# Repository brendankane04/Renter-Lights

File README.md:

# Renter Lights

Automatic light control which doesn't involve messing with your light switches & talking to your landlords

# Firmware 

## Files

**Wifi_Interface.cpp:** Driver to send TCP messages over wifi<br>
**SG90.cpp:** Driver for the SG90 servo, turns it on & off.<br>
**SR501.cpp:** Driver the SR501 PIR sensor. The handler init is can be run independently.<br>
**MQTT.cpp:** Initialization for MQTT events & central event handler.<br>
**pins.h:** definitions of relevant GPIO pins.<br>
**main.cpp:** main file. Combines all the modules.<br>

# Hardware

**Hardware.sch:** The schematics for the minimum unit<br>
**Hardware.kicad_pcb:** The layout file<br>

# Mechanical

# Backend

A mosquitto MQTT broker server on a raspberry pi is used to interface the devicecs. Just get one up & running.

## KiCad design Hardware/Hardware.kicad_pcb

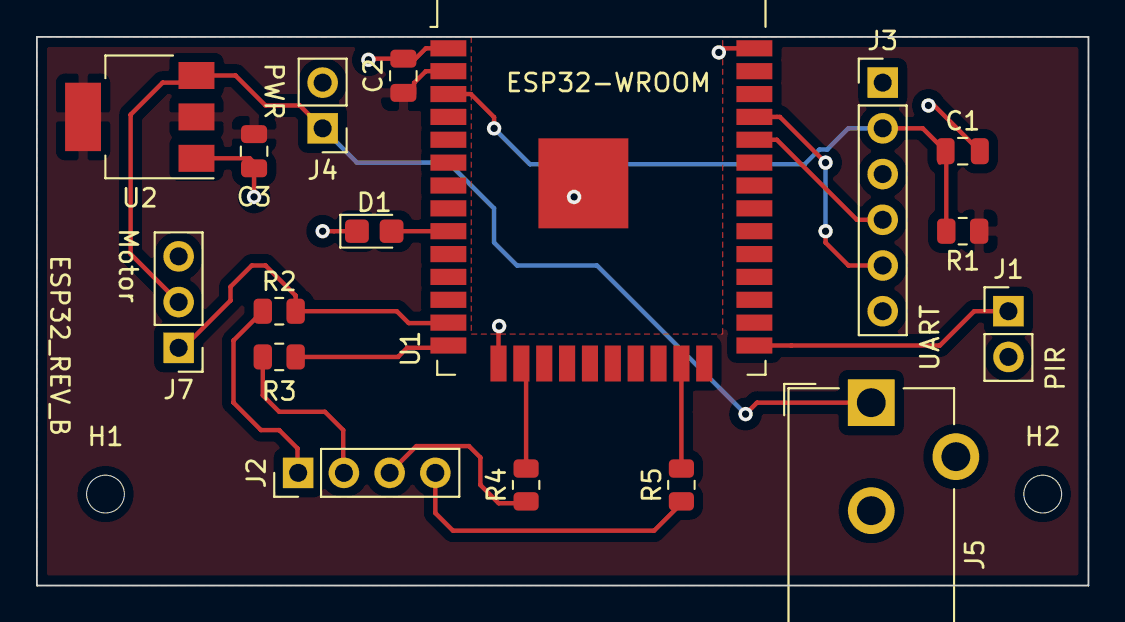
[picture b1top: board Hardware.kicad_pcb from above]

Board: 2 copper layers, 58.4 x 30.5 mm, 19 parts (0 on the bottom side), 16 nets.

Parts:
C1, C3: 0.1uF; C_0805_2012Metric
C2: 1uF; C_0805_2012Metric
D1: LED; LED_0805_2012Metric_Castellated
H1, H2: MountingHole; MountingHole_2.1mm
J1, J4: Conn_01x02; PinHeader_1x02_P2.54mm_Vertical
J2: Conn_01x04; PinHeader_1x04_P2.54mm_Vertical
J3: Conn_01x06; PinHeader_1x06_P2.54mm_Vertical
J5: Jack-DC; BarrelJack_CUI_PJ-102AH_Horizontal
J7: Conn_01x03; PinHeader_1x03_P2.54mm_Vertical
R1: 10K; R_0805_2012Metric
R2, R3, R4, R5: 100; R_0805_2012Metric
U1: ESP32-WROOM-32
U2: AMS1117-3.3; SOT-223-3_TabPin2

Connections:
/BATT_POS: J4.1, J5.1, J7.2, U2.3
/EN: C1.1, J3.2, R1.2, U1.3
/IO33: D1.2, U1.9
/MTCK: R4.2, U1.16
/MTDI: R3.2, U1.14
/MTDO: R5.2, U1.23
/MTMS: J7.1, R2.2, U1.13
/PIR_INPUT: J1.1, U1.25
/RXD: J3.4, U1.34
/TXD: J3.5, U1.35
/VDD33: C2.1, C3.1, R1.1, U1.2, U2.2
GND: C1.2, C2.2, C3.2, D1.1, J1.2, J3.1, J4.2, J5.2, J7.3, U1.1, U1.15, U1.38, U1.39, U2.1
unnamed: J2.1, R2.1
unnamed: J2.2, R3.1
unnamed: J2.3, R4.1
unnamed: J2.4, R5.1

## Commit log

2021-08-12 The README was made.
2021-08-17 The README was updated.
2021-08-29 A reference project/environment was added.
2021-08-30 Build experimenting was done.
2021-08-31 Quality of life improvements were made.
2021-09-01 Stepper motor testing was done.
2021-09-02 Servo control was added.
2021-09-03 The PIR sensor was tested.
2021-09-04 The servo code was simplified.
2021-09-05 Some basic control code was created.
2021-09-06 A basic control set of code was added.
2021-09-07 Servo code was exported.
2021-09-07 The class was finished.
2021-09-08 The build files were removed from the index.
2021-09-08 The SG90 driver was cleaned up.
2021-09-08 The SR501 driver was added.
2021-09-08 The gitignore was altered to ignore the build files.
2021-09-09 The project was converted to an eclipse IDF project to assist development.
2021-09-09 The build files will now be ignored.
2021-09-09 The original source directory was removed.
2021-09-10 The wifi interface was started.
2021-09-11 A datasheet was added to the PIR header file.
2021-09-12 The README was restored.
2021-09-13 The wifi driver was developed.
2021-09-13 The wifi driver was completed writing-wise, awaiting testing.
2021-09-15 Errors were removed from the wifi driver.
2021-09-16 A bug in the wifi was fixed.
2021-09-17 Wifi development was done.
2021-09-19 An extraneous file was removed.
2021-09-20 SOME version of a wrapper class was added. OMG, that was a waste of time.
2021-09-21 lwIP updates
2021-09-21 README update.
2021-09-23 A socket init was added.
2021-09-24 Eclipse settings
2021-09-25 Socket dev
2021-09-26 Some kinks were worked out.
2021-09-26 The send function was integrated. A lookover & rewrite is still necessary though. It's so messy.
2021-09-28 Wifi driver maintenance
2021-09-30 Wifi driver updates
2021-09-30 Error correction
2021-10-01 A streamlined wifi setup was added.
2021-10-01 Comments were added.
2021-10-02 Testing was done. Comments were added.
2021-10-03 Driver updates & testing
2021-10-04 The wifi & sensor controls were combined.
2021-10-05 Some sensor changes were started.
2021-10-06 Testing was done.
2021-10-07 Integration of IR sensor & RTOS
2021-10-07 Wifi and PIR updates
2021-10-09 Delay macros were added.
2021-10-09 Sensor updates
2021-10-11 Sensor class changes
2021-10-12 Global wifi interface
2021-10-14 Main changes
2021-10-15 Function name changed to an overload
2021-10-16 Testing was done
2021-10-17 Logging correction
2021-10-19 Testing
2021-10-20 Some tests were finalized.
2021-10-21 cleanup
2021-10-23 signal changes
2021-10-24 handler integration
2021-10-25 handler additions
2021-10-26 handler addition
2021-10-26 handler inclusion
2021-10-27 event loop integration
2021-10-31 semaphore implementation
2021-10-31 Turns out the mutex in wifi worked. It was seriously that easy. This has been a good week.
2021-11-01 semaphore integration
2021-11-02 bug fixing
2021-11-02 sensor testing
2021-11-04 function pointer instead
2021-11-04 event was swapped to a function pointer. yayyyyyy......
2021-11-04 removed scaffolding
2021-11-05 code cleanup
2021-11-07 servo handler started
2021-11-07 servo handler improvement
2021-11-07 removed event loop code from main.cpp
2021-11-07 more sensor code was removed
2021-11-07 task development
2021-11-07 servo integration completed.
2021-11-09 maximum degree reduced to reduce noise on servo
2021-11-10 Constants were added.
2021-11-11 header file cleanup
2021-11-12 readme update
2021-11-26 ignoring .bak files now, ugh.
2021-11-26 random stuff
2022-02-09 The hardware project was created.
2022-02-12 The schematic was started.
2022-02-13 Some hardware dev
2022-02-14 Basic hardware bringup for ESP32-WROOM
2022-02-15 Hardware dev
2022-02-17 Some footprints were fixed.
2022-02-17 Routing was done
2022-02-18 quality of life improvements
2022-02-20 Motor port addition and ground plane fix
2022-02-21 Silkscreen was added.
2022-02-21 battery connector update
2022-02-21 plane updates
2022-02-22 Code updates
2022-02-23 Footprint adjustments
2022-02-24 small cleanup in main
2022-02-25 config dev
2022-02-26 syntax fixes
2022-03-23 gitignore update
2022-04-10 SMD conversion
2022-04-10 Routings were finished.
2022-04-14 Added mounting holes
2022-04-16 README.md
2022-04-16 Fill was removed under MCU
2022-04-17 A board was bought. Yayyyyy!
2022-04-18 Some labeling to make the code more elegant
2022-04-20 connector fix
2022-04-22 A couple heap allocations were removed.
2022-04-22 Programmer fix
2022-04-24 layout reworking
2022-04-25 Layout updates
2022-04-25 Board revision
2022-04-27 board revising
2022-05-01 The final board was purchased
2022-05-06 Filament adjustment
2022-05-07 Filament change
2022-05-20 Removed singleton implementation
2022-05-20 device testing
2022-05-21 more device testing
2022-05-21 Some servo testing was done
2022-05-23 Some more reflow was done
2022-05-23 Reflow fixes
2022-05-25 More reflow correction
2022-05-26 JTAG setup
2022-05-27 String bug fix
2022-05-28 Scaffolding removed
2022-06-21 Implanted servo testing
2022-06-22 Chassis shrinking
2022-07-05 Servo pin fix
2022-07-07 Mosquitto testing on the pi
2022-07-08 MQTT testing
2022-07-09 MQTT is working
2022-07-10 MQTT integration
2022-07-11 MQTT & servo testing
2022-07-13 Voltage regulator & power drop testing
2022-07-16 Power supply testing
2022-07-19 Publishes added for the sensor
2022-07-20 Sensor logging & power supply testing
2022-07-22 Power supply fixes
2022-07-23 Decoupling cap fix & servo power rewire
2022-07-23 New gerbl created
2022-07-25 New pins file was created
2022-07-26 Operating mode refactoring
2022-07-27 File name normalization
2022-07-28 A servo was broken
2022-07-29 Sleep mode testing
2022-07-29 Sleep mode dev
2022-07-31 Wifi wakeup
2022-07-31 Barrel jack was added to board
2022-08-19 main rewrite
2022-09-11 Compatibility changes and complex development
2022-09-21 Testing & SDK config
2022-09-23 New wire placement
2022-09-24 New pin
2022-09-27 elegancy improvement
2022-10-05 upkeep
2022-10-07 const def
2023-01-22 PDF's were added for the hardware
